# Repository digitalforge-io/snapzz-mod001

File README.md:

# snapzz-mod001
SNAPZZ - Module-001 (ESP32-PICO-D4 based)

[Datasheet](/_asset/Datasheet.pdf)

[Schematics](/_asset/"schematics.pdf")

Licensed under:

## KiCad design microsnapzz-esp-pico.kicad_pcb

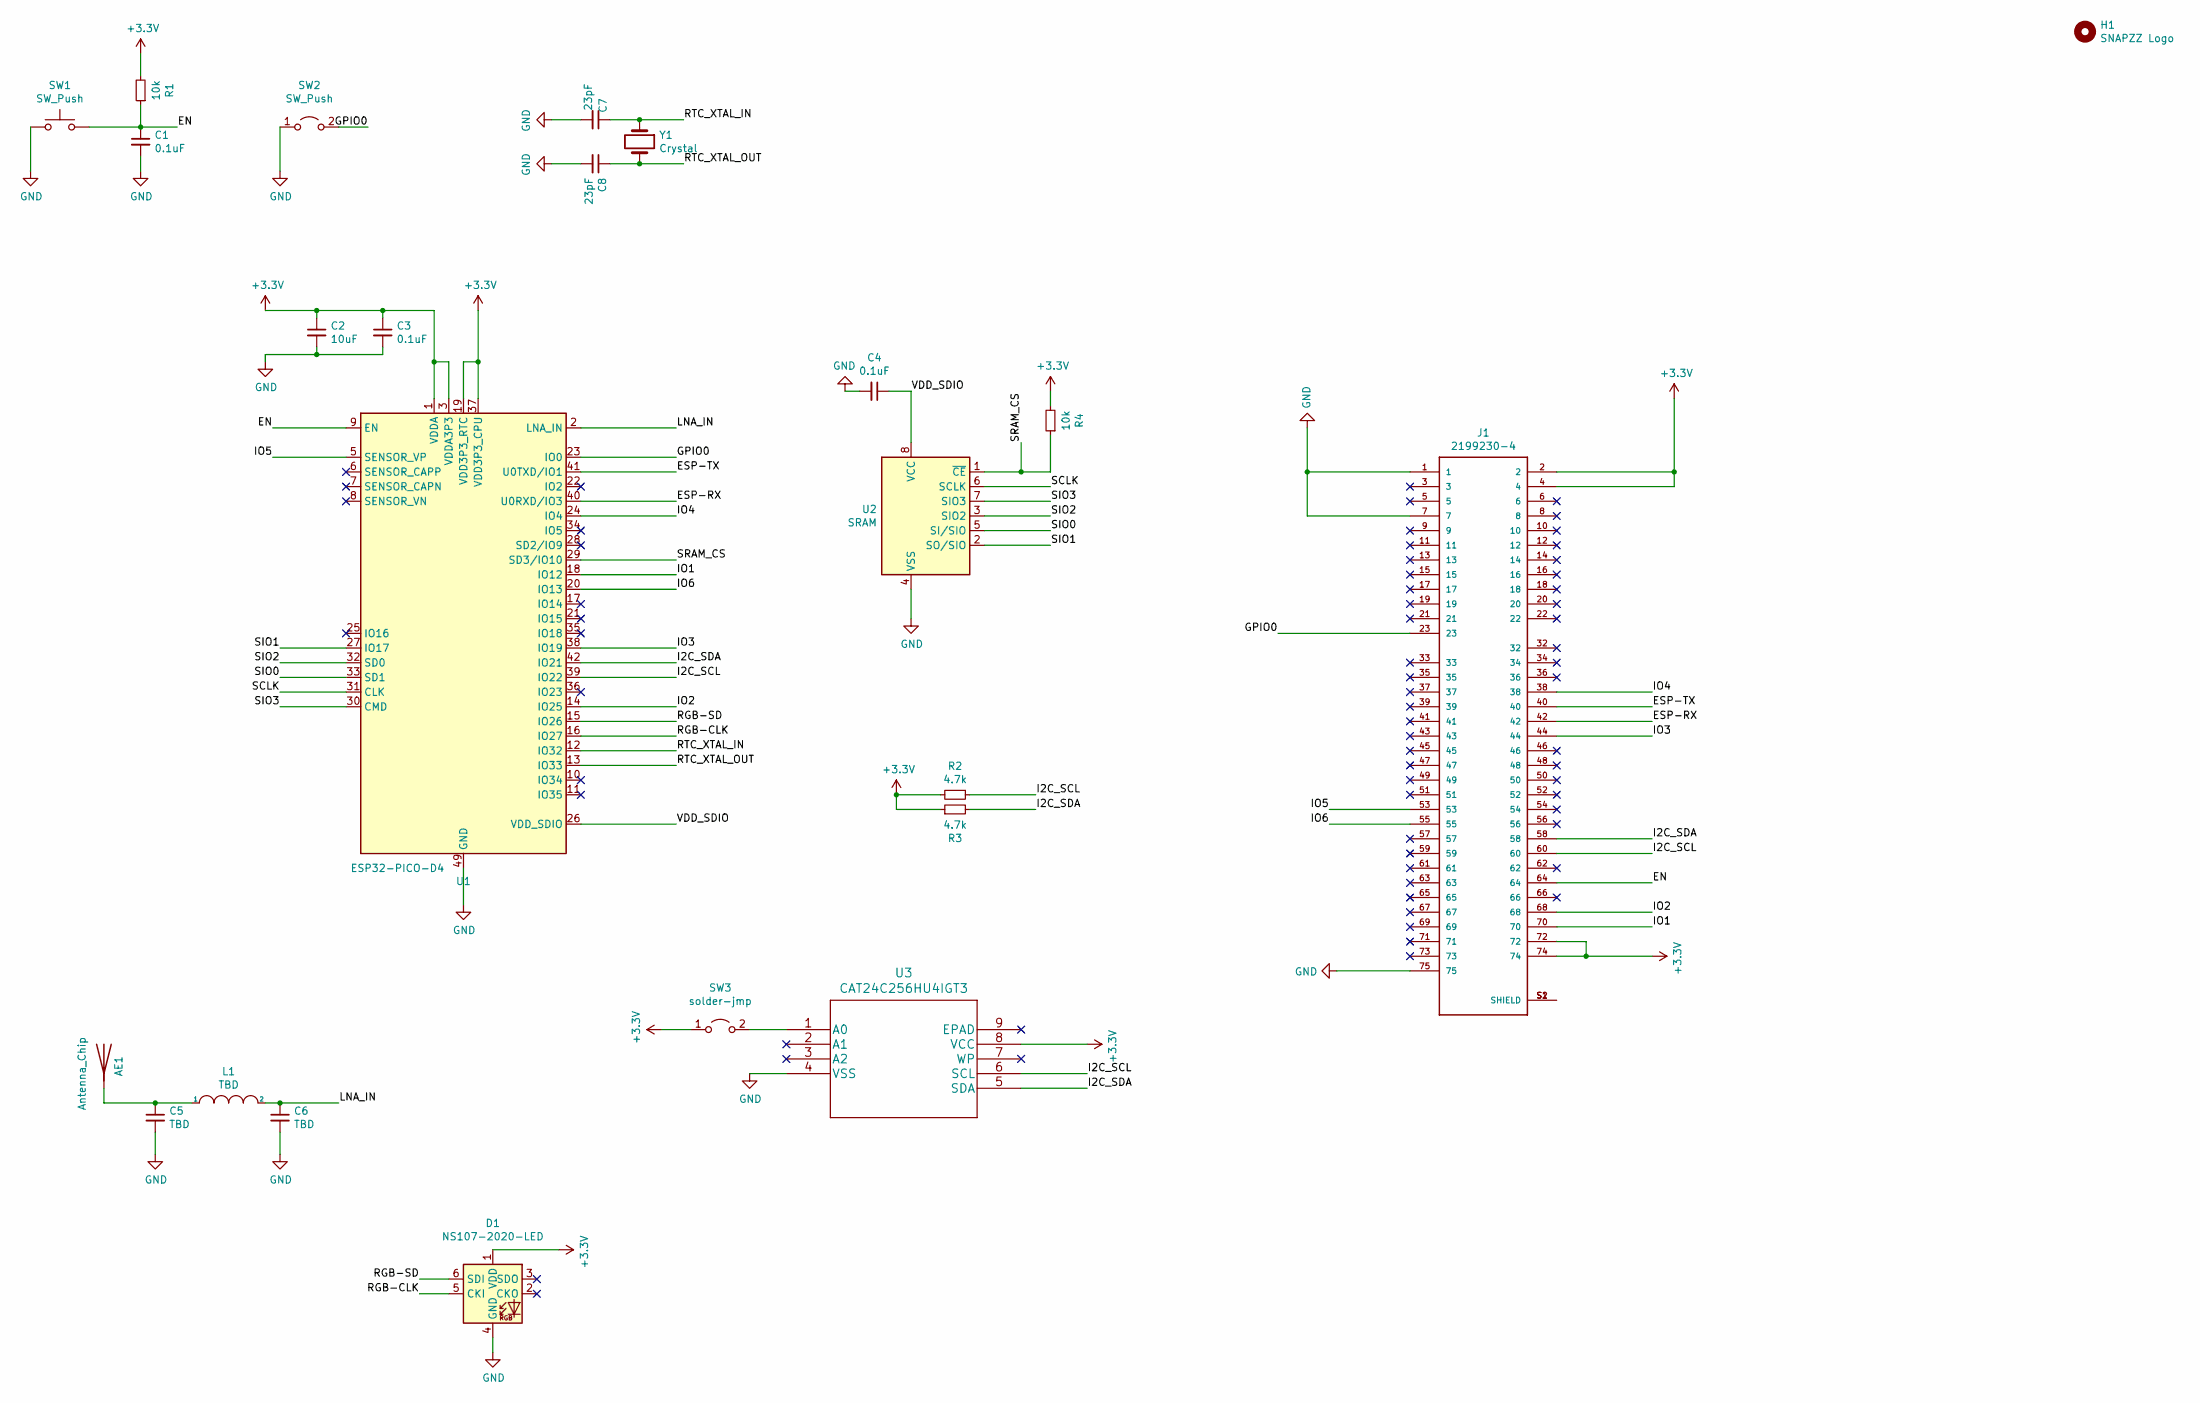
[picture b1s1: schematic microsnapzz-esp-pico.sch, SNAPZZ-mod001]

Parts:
AE1: Antenna_Chip; Johanson_2450AT43F0100
C1, C3, C4: 0.1uF; C_0402_1005Metric
C2: 10uF; C_0402_1005Metric
C5, C6: TBD; C_0402_1005Metric
C7, C8: 23pF; C_0402_1005Metric
D1: NS107-2020-LED; LED-LS8822-2020
H1: SNAPZZ Logo; snapzz-20x9
J1: 2199230-4; NGFF_E
L1: TBD; L_0402_1005Metric
R1, R4: 10k; R_0402_1005Metric
R2, R3: 4.7k; R_0402_1005Metric
SW1: SW_Push; SW_SPST_B3U-1000P
SW2: SW_Push; SolderJumper-2_P1.3mm_OPEN_RoundedPad1.0x1.5mm
SW3: solder-jmp; SolderJumper-2_P1.3mm_Open_RoundedPad1.0x1.5mm
U1: ESP32-PICO-D4; QFN-48-1EP_7x7mm_P0.5mm_EP5.3x5.3mm
U2: SRAM; SOIC-8_3.9x4.9mm_P1.27mm
U3: CAT24C256HU4IGT3; CAT24C256HU4IGT3-v2
Y1: Crystal; Crystal_SMD_G8-2Pin_3.2x1.5mm

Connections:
+3V3: C2.1, C3.1, D1.1 (VDD), J1.2, J1.4, J1.72, J1.74, R1.2, R2.2, R3.1, R4.2, SW3.1 (A), U1.1 (VDDA), U1.3 (VDDA3P3), U1.4 (VDDA3P3), U1.19 (VDD3P3_RTC), U1.37 (VDD3P3_CPU), U1.43 (VDDA), U1.46 (VDDA), U3.8 (VCC)
/EN: C1.1, J1.64, R1.1, SW1.2, U1.9 (EN)
/ESP-RX: J1.42, U1.40 (U0RXD/IO3)
/ESP-TX: J1.40, U1.41 (U0TXD/IO1)
/GPIO0: J1.23, SW2.2 (B), U1.23 (IO0)
/I2C_SCL: J1.60, R2.1, U1.39 (IO22), U3.6 (SCL)
/I2C_SDA: J1.58, R3.2, U1.42 (IO21), U3.5 (SDA)
/IO1: J1.70, U1.18 (IO12)
/IO2: J1.68, U1.14 (IO25)
/IO3: J1.44, U1.38 (IO19)
/IO4: J1.38, U1.24 (IO4)
/IO5: J1.53, U1.5 (SENSOR_VP)
/IO6: J1.55, U1.20 (IO13)
/LNA_IN: C6.1, L1.2, U1.2 (LNA_IN)
/RGB-CLK: D1.5 (CKI), U1.16 (IO27)
/RGB-SD: D1.6 (SDI), U1.15 (IO26)
/RTC_XTAL_IN: C7.1, U1.12 (IO32), Y1.1
/RTC_XTAL_OUT: C8.1, U1.13 (IO33), Y1.2
/SCLK: U1.31 (CLK), U2.6 (SCLK)
/SIO0: U1.33 (SD1), U2.5 (SI/SIO)
/SIO1: U1.27 (IO17), U2.2 (SO/SIO)
/SIO2: U1.32 (SD0), U2.3 (SIO2)
/SIO3: U1.30 (CMD), U2.7 (SIO3)
/SRAM_CS: R4.1, U1.29 (SD3/IO10), U2.1 (~CE)
/VDD_SDIO: C4.1, U1.26 (VDD_SDIO), U2.8 (VCC)
GND: C1.2, C2.2, C3.2, C4.2, C5.2, C6.2, C7.2, C8.2, D1.4 (GND), J1.1, J1.7, J1.75, SW1.1, SW2.1 (A), U1.49 (GND), U2.4 (VSS), U3.4 (VSS)
unnamed: AE1.1, C5.1, L1.1
unnamed: SW3.2 (B), U3.1 (A0)

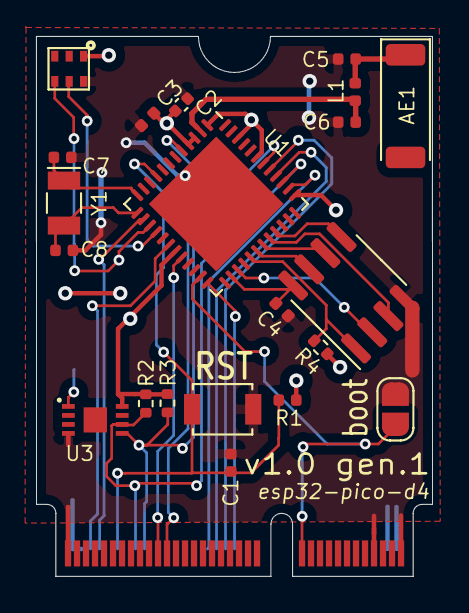
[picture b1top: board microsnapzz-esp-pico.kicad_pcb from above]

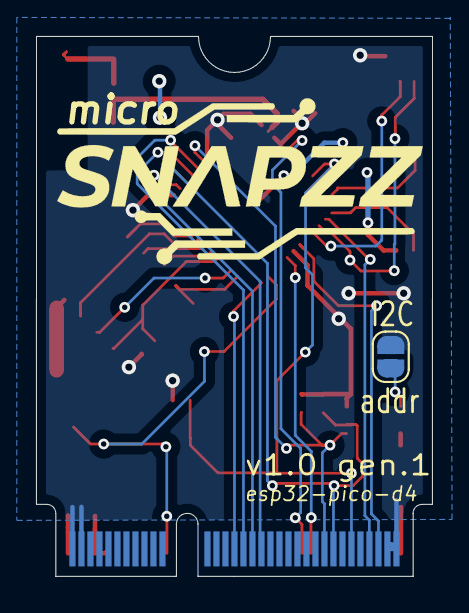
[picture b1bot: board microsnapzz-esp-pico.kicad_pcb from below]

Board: 2 copper layers, 22.0 x 30.0 mm, 24 parts (2 on the bottom side), 28 nets.

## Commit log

2020-10-24 readme
2020-10-25 add DS
2020-10-30 add License & update DS
2020-10-30 errata DS
2020-10-30 correct DS link
2020-10-30 fix link
2020-10-30 cleanup assets
2020-10-30 rename/word files
